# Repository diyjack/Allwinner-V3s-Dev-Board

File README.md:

# Allwinner-V3s-Dev-Board
Entwicklungsplatine für den nicht sehr bekannten V3s Soc von Allwinner. <br>In dieser Version wurde speziell auf die Multimedia Interfaces des V3s verzichtet um das Entwicklungsboard so einfach wie möglich zu halten.<br> Das Entwicklungsboard verfügt über eine 100mbit Ethernet Buchse,
einen USB Host, ein MIPI Kamera Interface(welches kompatibel zur Raspberry Pi Kamera ist), desweiteren kann über eine micro SD-Karte gebootet werden.<br>
Das Entwicklungsboard verfügt über 12 Eingänge / Ausgänge die auf einer Wago-Klemme aufgelegt sind.<br>Das Entwicklungsboard kann mit bis zu 35V DC betrieben werden.<br> Dieses Entwicklungsboard wurde für die Verwendung im industriellen Bereich entwickelt.
Der CO-Prozessor (ATmega328) überwacht die Eingänge und kann ggf. auch geringe Lasten schalten. 

Die Gerber Dateien und der Schaltplan wurden unter der Open Source Hardware Lizenz veröffentlicht und dürfen für den nicht kommerziellen Zweck gerne weiter verwendet werden.

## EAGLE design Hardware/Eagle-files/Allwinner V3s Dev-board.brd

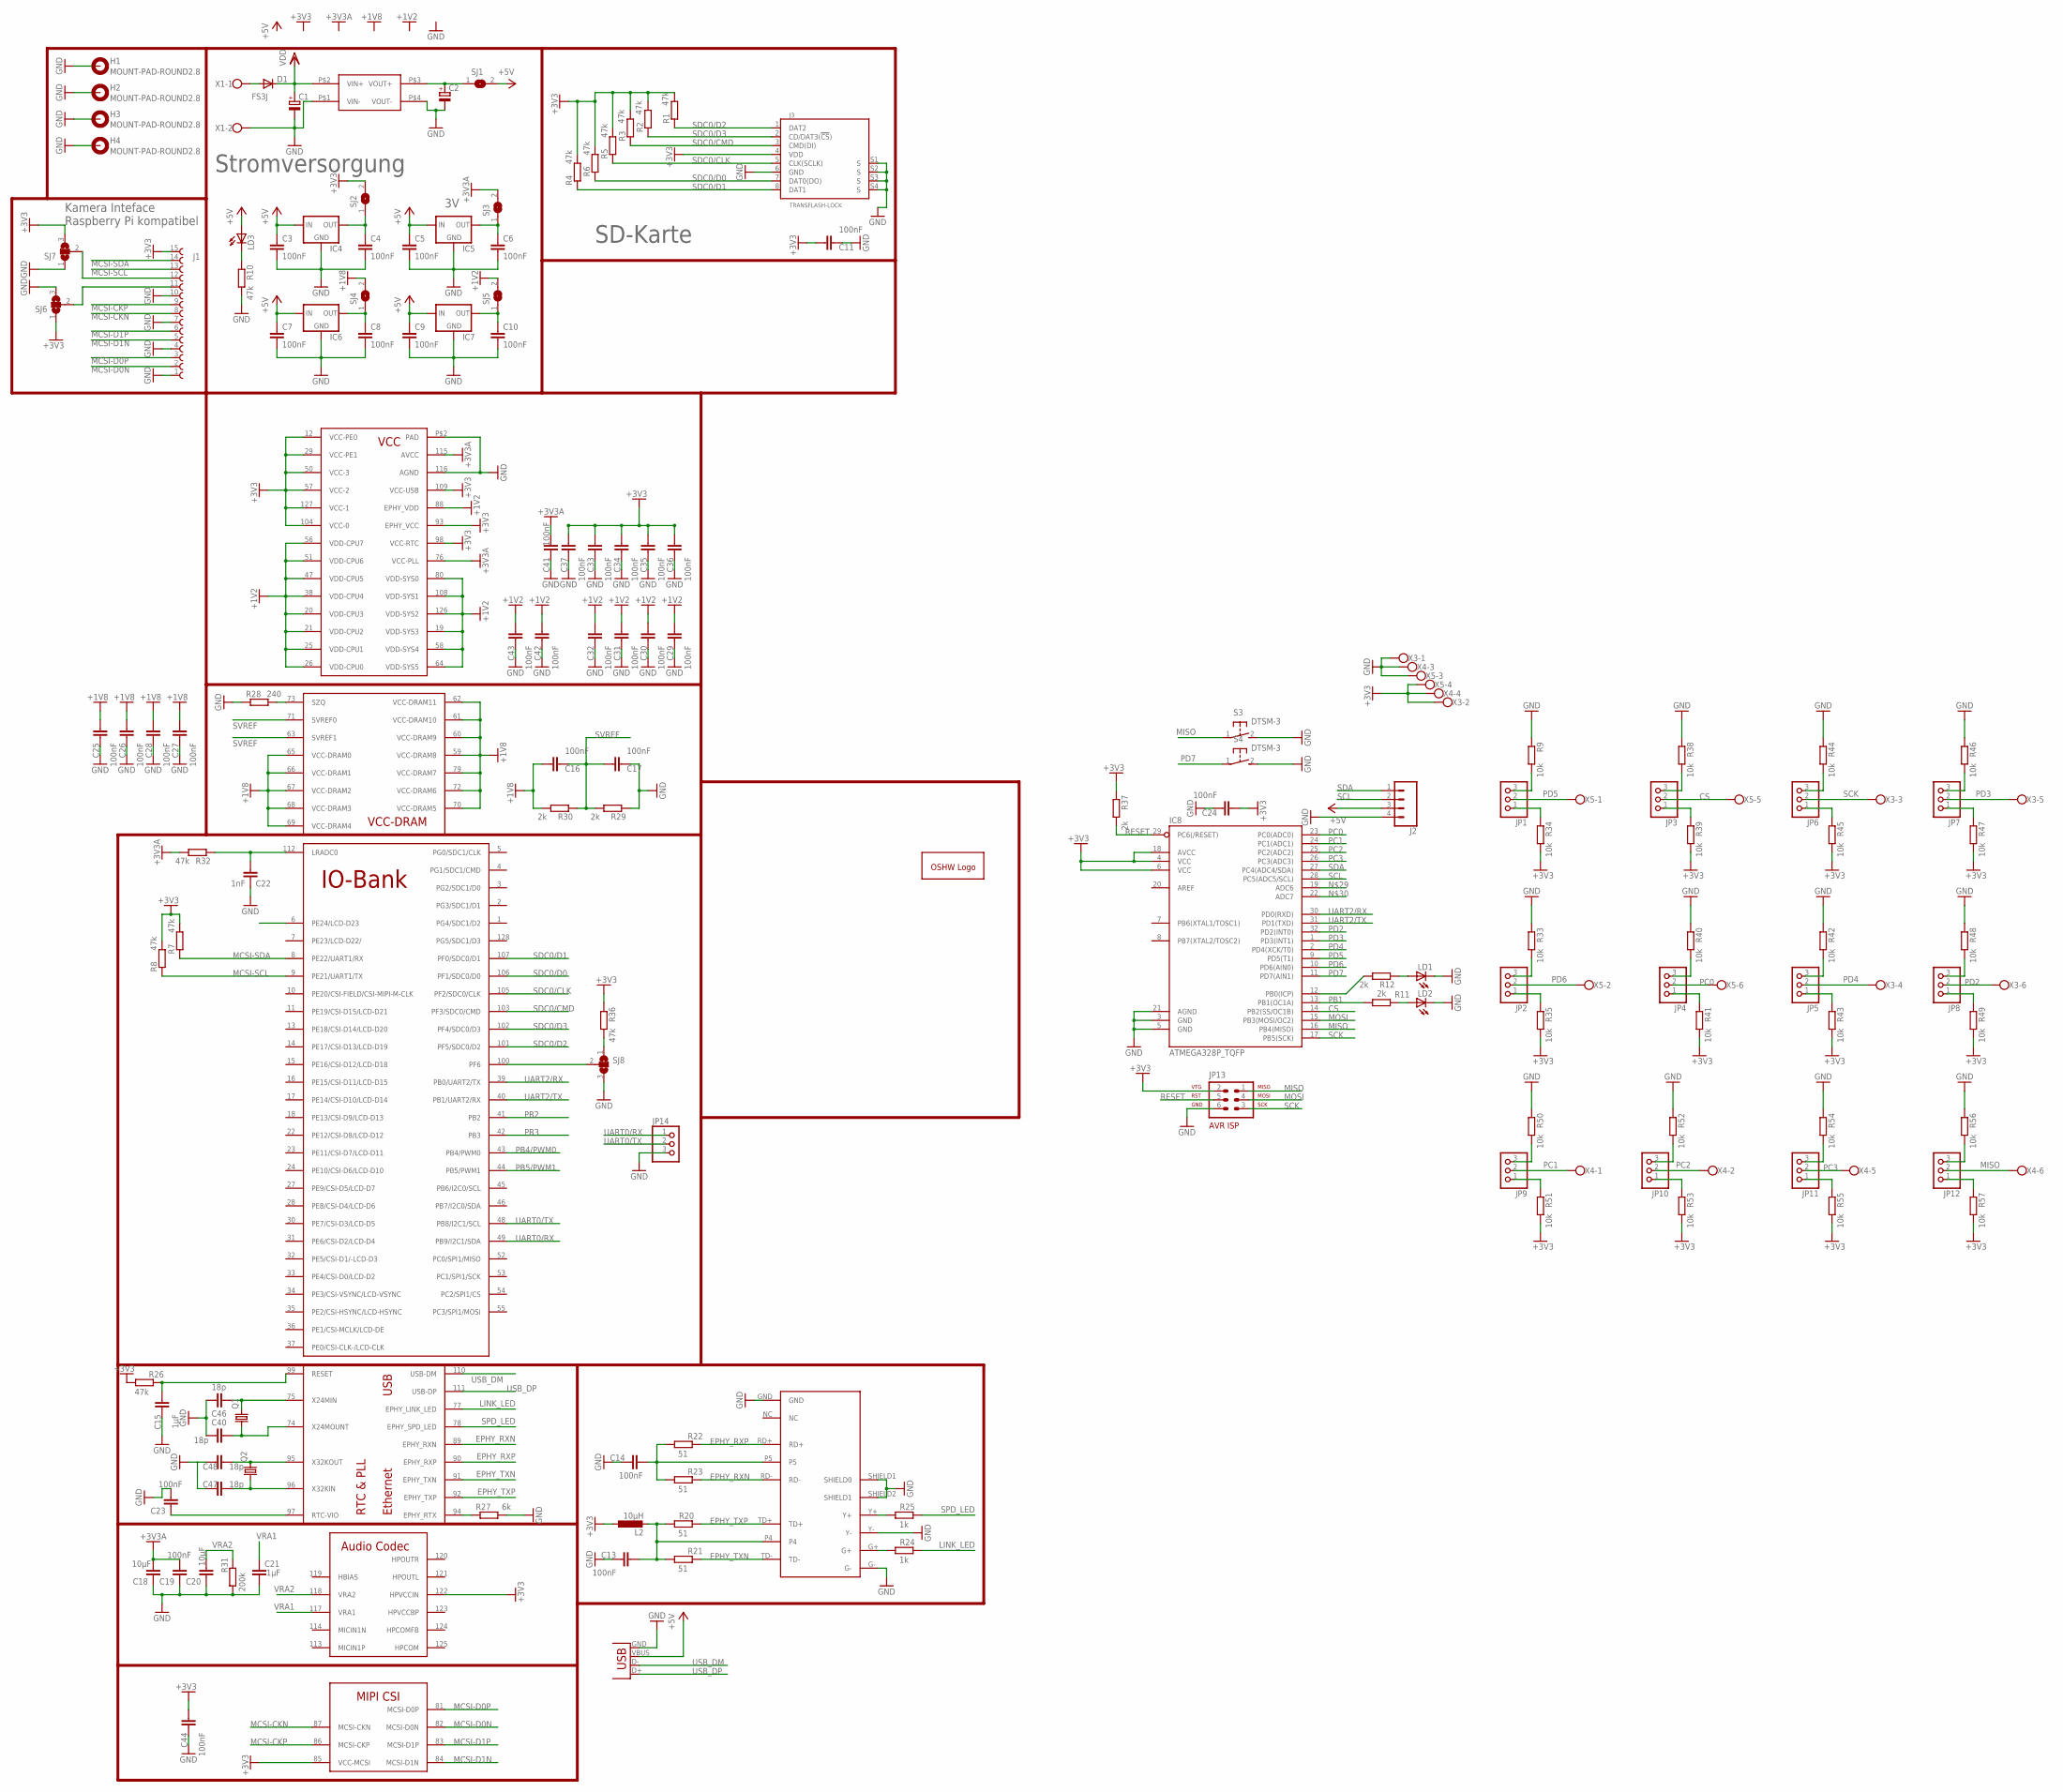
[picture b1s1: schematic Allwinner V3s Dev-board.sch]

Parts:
C1, C2: CPOL-EU153CLV-0807; 153CLV-0807
C3, C4, C5, C6, C7, C8, C9, C10, C11, C13, C14, C16, C17, C19, C23, C24, C25, C26, C27, C28, C29, C30, C31, C32, C33, C34, C35, C36, C37, C41, C42, C43, C44: 100nF; C0805
C15, C21: 1µF; C0805
C18, C20: 10µF; C0805
C22: 1nF; C0805
C40, C46, C47, C48: 18p; C0805
D1: FS3J; SMC
GOLD_ORB_SM2: OSHWLOGOLOGO8MM; OSHW_8MM
H1, H2, H3, H4: MOUNT-PAD-ROUND2.8; 2,8-PAD
IC1: V3S; QFP-128
IC4, IC5, IC6, IC7: LM1117; SOT223
IC8: ATMEGA328P_TQFP; TQFP32-08
J1: 68611514122
J2: CONN_04SMD_LONG; 1X04_SMD_LONG
J3: TRANSFLASH-LOCK; TRANSFLASH-LOCK-SOCK
JP1, JP2, JP3, JP4, JP5, JP6, JP7, JP8, JP9, JP10, JP11, JP12, JP14: PINHD-1X3; 1X03
JP13: AVR-ISP-6
L2: 10µH; L0805
LD1, LD2, LD3: LEDSMT1206; 1206
M1: MP1584-MINI; MINI-DC-BRICK
Q1: CRYSTALHC49S; HC49/S
Q2: CRYSTALTC26H; TC26H
R1, R2, R3, R4, R5, R6, R7, R8, R10, R26, R32, R36: 47k; R0805
R9, R33, R34, R35, R38, R39, R40, R41, R42, R43, R44, R45, R46, R47, R48, R49, R50, R51, R52, R53, R54, R55, R56, R57: 10k; R0805
R11, R12, R29, R30, R37: 2k; R0805
R20, R21, R22, R23: 51; R0805
R24, R25: 1k; R0805
R27: 6k; R0805
R28: 240; R0805
R31: 200k; R0805
S3, S4: DTSM-3
SJ1, SJ2, SJ3, SJ4, SJ5: SJ
SJ6, SJ7, SJ8: SJ2W; SJ_2
U$3: HR911105A; RJ45
X1: W237-102
X2: USB-A-H
X3, X4, X5: W237-6

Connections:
+1V2: C29.1, C30.1, C31.1, C32.1, C42.1, C43.1, IC1.19 (VDD-SYS3), IC1.20 (VDD-CPU3), IC1.21 (VDD-CPU2), IC1.25 (VDD-CPU1), IC1.26 (VDD-CPU0), IC1.38 (VDD-CPU4), IC1.47 (VDD-CPU5), IC1.51 (VDD-CPU6), IC1.56 (VDD-CPU7), IC1.58 (VDD-SYS4), IC1.64 (VDD-SYS5), IC1.80 (VDD-SYS0), IC1.88 (EPHY_VDD), IC1.108 (VDD-SYS1), IC1.126 (VDD-SYS2), SJ5.2
+1V8: C16.1, C25.1, C26.1, C27.1, C28.1, IC1.59 (VCC-DRAM8), IC1.60 (VCC-DRAM9), IC1.61 (VCC-DRAM10), IC1.62 (VCC-DRAM11), IC1.65 (VCC-DRAM0), IC1.66 (VCC-DRAM1), IC1.67 (VCC-DRAM2), IC1.68 (VCC-DRAM3), IC1.69 (VCC-DRAM4), IC1.70 (VCC-DRAM5), IC1.72 (VCC-DRAM6), IC1.79 (VCC-DRAM7), R30.2, SJ4.2
+3V3: C11.1, C24.1, C33.1, C34.1, C35.1, C36.1, C37.1, C44.1, IC1.12 (VCC-PE0), IC1.29 (VCC-PE1), IC1.50 (VCC-3), IC1.57 (VCC-2), IC1.85 (VCC-MCSI), IC1.93 (EPHY_VCC), IC1.98 (VCC-RTC), IC1.104 (VCC-0), IC1.109 (VCC-USB), IC1.122 (HPVCCIN), IC1.127 (VCC-1), IC8.4 (VCC), IC8.6 (VCC), IC8.18 (AVCC), J1.15 (1), J3.4 (VDD), JP13.2, L2.1, R1.2, R2.2, R3.2, R4.2, R5.2, R6.2, R7.2, R8.2, R26.2, R34.2, R35.2, R36.1, R37.1, R39.2, R41.2, R43.2, R45.2, R47.2, R49.2, R51.2, R53.2, R55.2, R57.2, SJ2.2, SJ6.1, SJ7.3, X3.2, X4.4, X5.4
+3V3A: C18.1, C19.1, C41.1, IC1.76 (VCC-PLL), IC1.115 (AVCC), R32.2, SJ3.2
+5V: C3.1, C5.1, C7.1, C9.1, IC4.3 (IN), IC5.3 (IN), IC6.3 (IN), IC7.3 (IN), J2.3, LD3.A, SJ1.2, X2.VBUS
CS: IC8.14 (PB2(SS/OC1B)), JP3.2, X5.5
EPHY_RXN: IC1.89 (EPHY_RXN), R23.1, U$3.RD-
EPHY_RXP: IC1.90 (EPHY_RXP), R22.1, U$3.RD+
EPHY_TXN: IC1.91 (EPHY_TXN), R21.1, U$3.TD-
EPHY_TXP: IC1.92 (EPHY_TXP), R20.1, U$3.TD+
GND: C1.-, C2.-, C3.2, C4.2, C5.2, C6.2, C7.2, C8.2, C9.2, C10.2, C11.2, C13.2, C14.2, C15.2, C17.2, C18.2, C19.2, C20.2, C21.2, C22.1, C23.1, C24.2, C25.2, C26.2, C27.2, C28.2, C29.2, C30.2, C31.2, C32.2, C33.2, C34.2, C35.2, C36.2, C37.2, C40.1, C41.2, C42.2, C43.2, C44.2, C46.1, C47.1, C48.1, H1.B2,8, H2.B2,8, H3.B2,8, H4.B2,8, IC1.116 (AGND), IC1.P$2 (PAD), IC4.1 (GND), IC5.1 (GND), IC6.1 (GND), IC7.1 (GND), IC8.3 (GND), IC8.5 (GND), IC8.21 (AGND), J1.1 (15), J1.4 (12), J1.7 (9), J1.10 (6), J2.4, J3.6 (GND), J3.S1 (S), J3.S2 (S), J3.S3 (S), J3.S4 (S), JP13.6, JP14.3, LD1.C, LD2.C, M1.P$1 (VIN-), M1.P$4 (VOUT-), R9.1, R10.2, R27.2, R28.1, R29.1, R31.2, R33.1, R38.1, R40.1, R42.1, R44.1, R46.1, R48.1, R50.1, R52.1, R54.1, R56.1, S3.2, S4.2, SJ6.3, SJ7.1, SJ8.3, U$3.G-, U$3.GND, U$3.SHIELD1 (SHIELD0), U$3.SHIELD2 (SHIELD1), U$3.Y-, X1.2, X2.GND, X3.1, X4.3, X5.3
LINK_LED: IC1.77 (EPHY_LINK_LED), R24.1
MCSI-CKN: IC1.87 (MCSI-CKN), J1.8
MCSI-CKP: IC1.86 (MCSI-CKP), J1.9 (7)
MCSI-D0N: IC1.82 (MCSI-D0N), J1.2 (14)
MCSI-D0P: IC1.81 (MCSI-D0P), J1.3 (13)
MCSI-D1N: IC1.84 (MCSI-D1N), J1.5 (11)
MCSI-D1P: IC1.83 (MCSI-D1P), J1.6 (10)
MCSI-SCL: IC1.9 (PE21/UART1/TX), J1.13 (3), R8.1
MCSI-SDA: IC1.8 (PE22/UART1/RX), J1.14 (2), R7.1
MISO: IC8.16 (PB4(MISO)), JP12.2, JP13.1, S3.1, X4.6
MOSI: IC8.15 (PB3(MOSI/OC2)), JP13.4
unnamed: D1.A, X1.1
unnamed: JP2.3, R33.2
unnamed: JP1.3, R9.2
unnamed: C15.1, IC1.99 (RESET), R26.1
unnamed: LD1.A, R12.1
unnamed: LD3.C, R10.1
unnamed: JP1.1, R34.1
unnamed: J1.11 (5), SJ6.2
unnamed: J1.12 (4), SJ7.2
unnamed: IC8.12 (PB0(ICP)), R12.2
unnamed: JP2.1, R35.1
unnamed: JP3.3, R38.2
unnamed: JP3.1, R39.1
unnamed: JP4.3, R40.2
unnamed: C2.+, M1.P$3 (VOUT+), SJ1.1
unnamed: JP4.1, R41.1
unnamed: IC1.94 (EPHY_RTX), R27.1
unnamed: R24.2, U$3.G+
unnamed: IC1.73 (SZQ), R28.2
unnamed: R25.2, U$3.Y+
unnamed: C13.1, L2.2, R20.2, R21.2, U$3.P4
unnamed: C14.1, R22.2, R23.2, U$3.P5
unnamed: C22.2, IC1.112 (LRADC0), R32.1
unnamed: C23.2, IC1.97 (RTC-VIO)
unnamed: IC1.100 (PF6), SJ8.2
unnamed: R36.2, SJ8.1
unnamed: JP5.3, R42.2
unnamed: JP5.1, R43.1
unnamed: JP6.3, R44.2
unnamed: JP6.1, R45.1
unnamed: JP7.3, R46.2
unnamed: JP7.1, R47.1
unnamed: JP8.3, R48.2
unnamed: JP8.1, R49.1
unnamed: JP9.3, R50.2
unnamed: JP9.1, R51.1
unnamed: JP10.3, R52.2
unnamed: JP10.1, R53.1
unnamed: C4.1, IC4.2 (OUT), SJ2.1
unnamed: C6.1, IC5.2 (OUT), SJ3.1
unnamed: C8.1, IC6.2 (OUT), SJ4.1
unnamed: C10.1, IC7.2 (OUT), SJ5.1
unnamed: C40.2, IC1.74 (X24MOUNT), Q1.1
unnamed: C46.2, IC1.75 (X24MIN), Q1.2
unnamed: C47.2, IC1.96 (X32KIN), Q2.1
unnamed: C48.2, IC1.95 (X32KOUT), Q2.2
unnamed: JP11.3, R54.2
unnamed: JP11.1, R55.1
unnamed: JP12.3, R56.2
unnamed: JP12.1, R57.1
unnamed: LD2.A, R11.1
PB1: IC8.13 (PB1(OC1A)), R11.2
PB2: IC1.41 (PB2)
PB3: IC1.42 (PB3)
PB4/PWM0: IC1.43 (PB4/PWM0)
PB5/PWM1: IC1.44 (PB5/PWM1)
PC0: IC8.23 (PC0(ADC0)), JP4.2, X5.6
PC1: IC8.24 (PC1(ADC1)), JP9.2, X4.1
PC2: IC8.25 (PC2(ADC2)), JP10.2, X4.2
PC3: IC8.26 (PC3(ADC3)), JP11.2, X4.5
PD2: IC8.32 (PD2(INT0)), JP8.2, X3.6
PD3: IC8.1 (PD3(INT1)), JP7.2, X3.5
PD4: IC8.2 (PD4(XCK/T0)), JP5.2, X3.4
PD5: IC8.9 (PD5(T1)), JP1.2, X5.1
PD6: IC8.10 (PD6(AIN0)), JP2.2, X5.2
PD7: IC8.11 (PD7(AIN1)), S4.1
RESET: IC8.29 (PC6(/RESET)), JP13.5, R37.2
SCK: IC8.17 (PB5(SCK)), JP6.2, JP13.3, X3.3
SCL: IC8.28 (PC5(ADC5/SCL)), J2.2
SDA: IC8.27 (PC4(ADC4/SDA)), J2.1
SDC0/CLK: IC1.105 (PF2/SDC0/CLK), J3.5 (CLK(SCLK)), R5.1
SDC0/CMD: IC1.103 (PF3/SDC0/CMD), J3.3 (CMD(DI)), R3.1
SDC0/D0: IC1.106 (PF1/SDC0/D0), J3.7 (DAT0(DO)), R6.1
SDC0/D1: IC1.107 (PF0/SDC0/D1), J3.8 (DAT1), R4.1
SDC0/D2: IC1.101 (PF5/SDC0/D2), J3.1 (DAT2), R1.1
SDC0/D3: IC1.102 (PF4/SDC0/D3), J3.2 (CD/DAT3(!CS!)), R2.1
SPD_LED: IC1.78 (EPHY_SPD_LED), R25.1
SVREF: C16.2, C17.1, IC1.63 (SVREF1), IC1.71 (SVREF0), R29.2, R30.1
UART0/RX: IC1.49 (PB9/I2C1/SDA), JP14.1
UART0/TX: IC1.48 (PB8/I2C1/SCL), JP14.2
UART2/RX: IC1.39 (PB0/UART2/TX), IC8.30 (PD0(RXD))
UART2/TX: IC1.40 (PB1/UART2/RX), IC8.31 (PD1(TXD))
USB_DM: IC1.110 (USB-DM), X2.D-
USB_DP: IC1.111 (USB-DP), X2.D+
VDD: C1.+, D1.C, M1.P$2 (VIN+)
VRA1: C21.1, IC1.117 (VRA1)
VRA2: C20.1, IC1.118 (VRA2), R31.1

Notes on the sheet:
Stromversorgung
Kamera Inteface Raspberry Pi kompatibel
SD-Karte

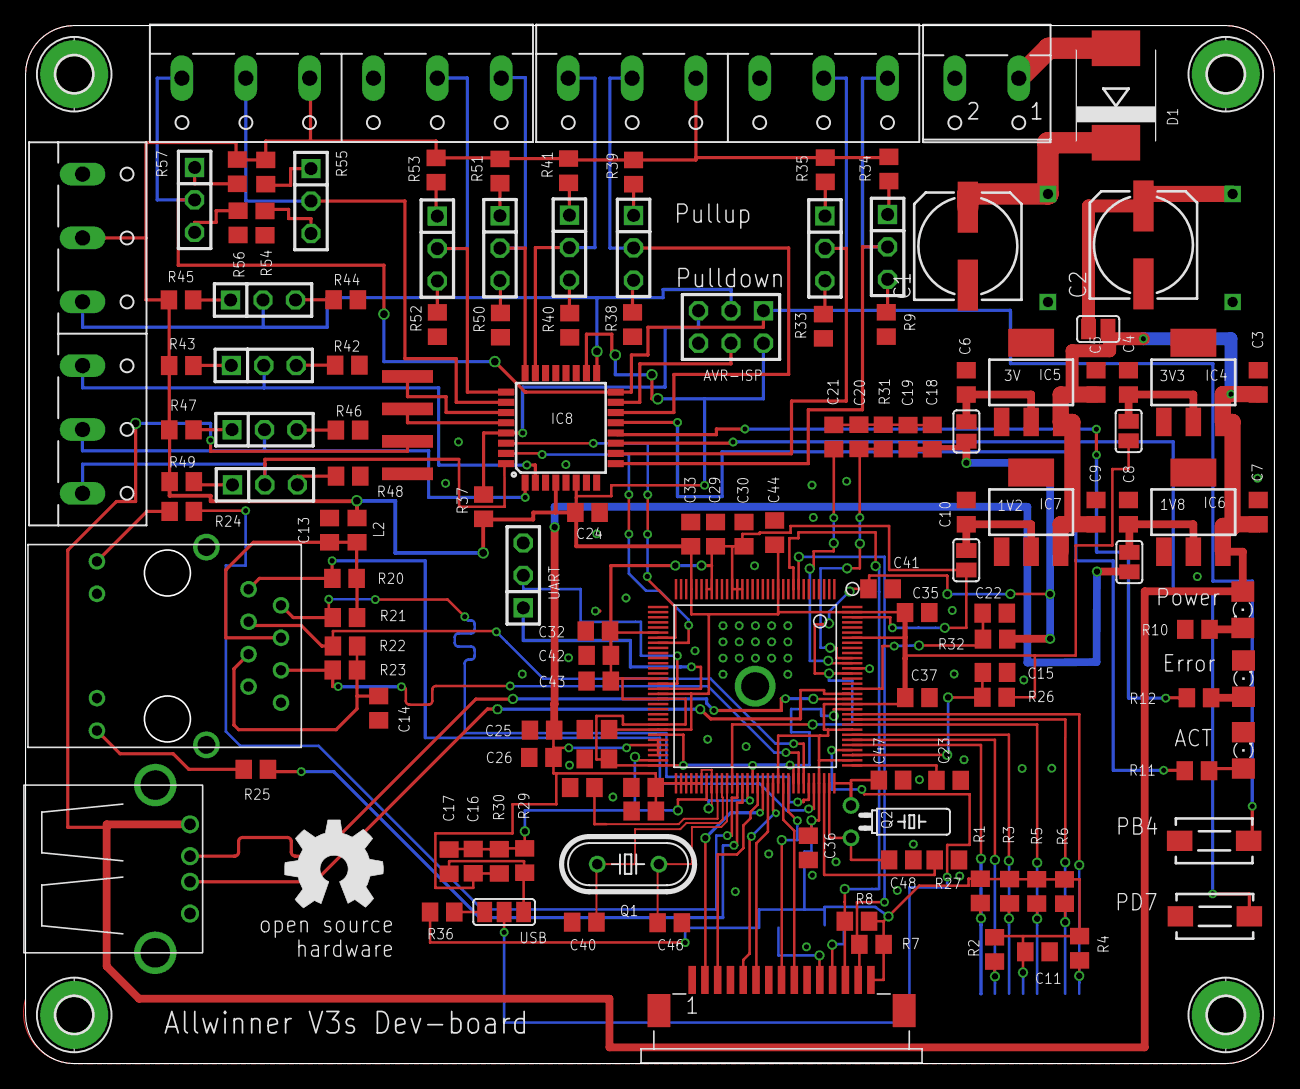
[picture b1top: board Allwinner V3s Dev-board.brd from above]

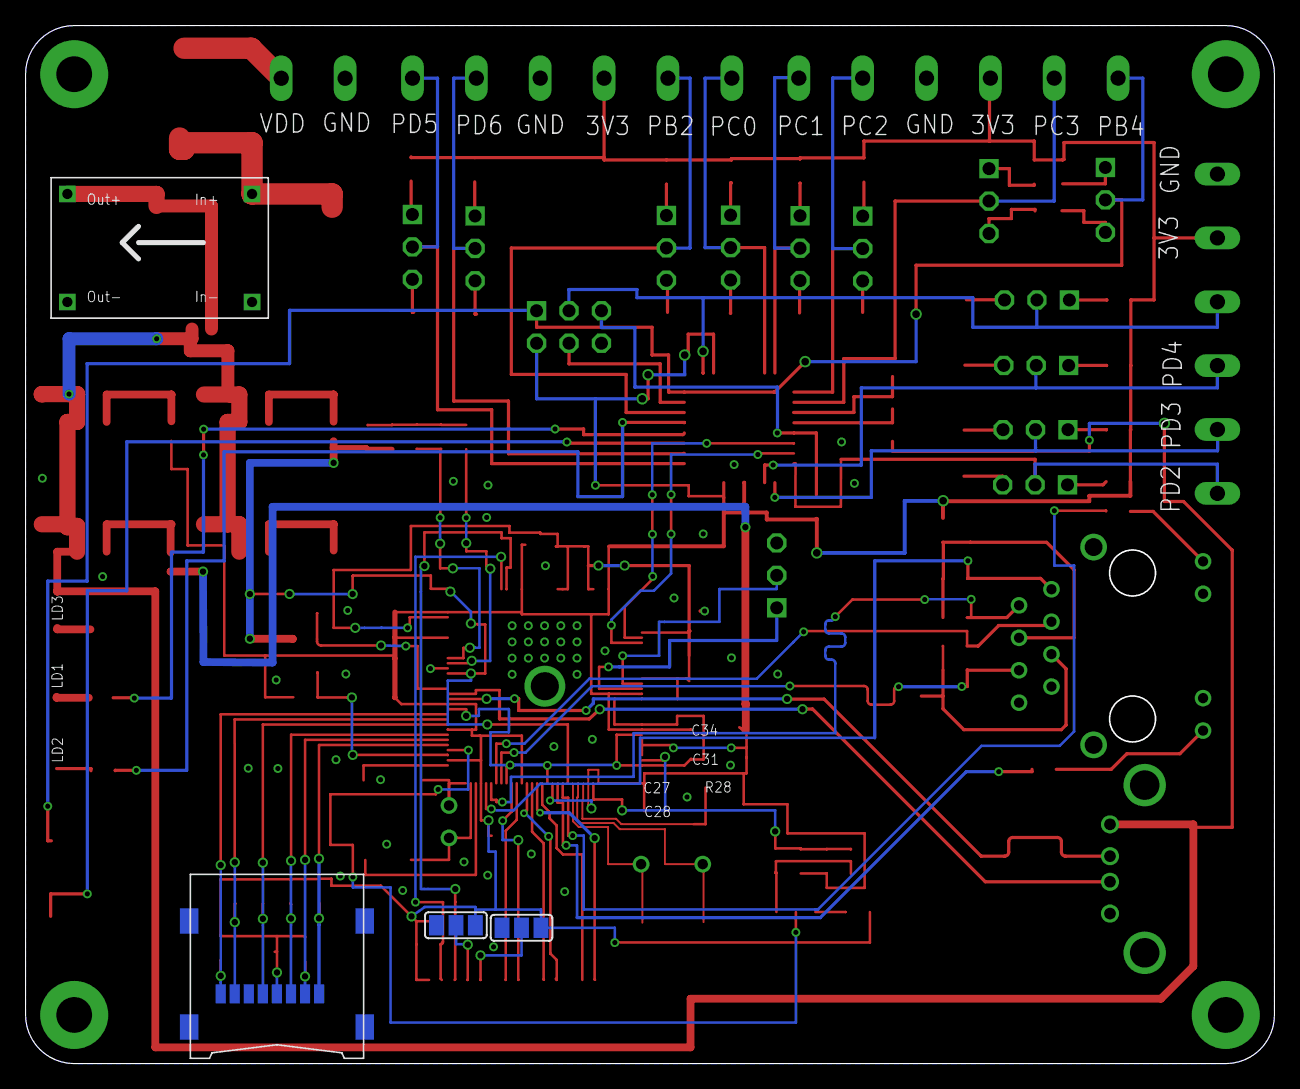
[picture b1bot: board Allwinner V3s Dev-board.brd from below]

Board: 2 copper layers, 97.8 x 81.3 mm, 146 parts (4 on the bottom side), 105 nets.

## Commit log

2017-06-21 Added new files

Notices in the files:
parts and their libraries:
EAGLE-FPC_CONNECTOR_AND_FFC_CAB-rev16b: Copyright: Würth Elektronik
SparkFun-IC-Microcontroller: Licensing: Creative Commons ShareAlike 4.0 International - https://creativecommons.org/licenses/by-sa/4.0
supply0: Copyright (C) 2007, Bob Starr
